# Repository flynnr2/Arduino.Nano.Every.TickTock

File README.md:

# Arduino Pendulum Timer

Capture firmware, logging and display software, and analysis tooling for high-precision pendulum timing.

## System Layout

```text
Arduino.Pendulum.Timer/
├── Nano.Every/         Precision capture firmware
├── Uno.R4.Deprecated/  Deprecated Uno receiver, retained for reference
├── Raspberry.Pi/       Pi Zero 2 W receiver, sensors, OLED and web
├── Docs/               System, protocol and component documentation
├── tests/              Capture, Pi, analysis and deprecated Uno tests
├── tools/              Minimal Nano serial capture tool
└── pendulum_analysis/  Offline clock and swing analysis
```

This is the combined repository for the complete Arduino Pendulum Timer (A.P.T)
system. The Nano Every timestamps pendulum and PPS events. A receiver handles storage,
environmental measurements, display and network access. The deprecated Uno receiver
and the Raspberry Pi replacement live here alongside the capture firmware.

- [Deprecated Uno R4 setup and validation](Uno.R4.Deprecated/README.md)
- [Raspberry Pi receiver and quickstart](Raspberry.Pi/README.md)
- [Hardware designs and prototype build files](Hardware/README.md)
- [Display repository import and provenance](Docs/Uno.R4.Deprecated/IMPORT.md)

The former `Arduino.Pendulum.Timer.Display` repository provides historical reference;
all maintained system components now belong here.

## What Is This?

The firmware captures pendulum beam-crossing edges and GPS PPS pulses on a shared ATmega4809 timer base, then emits serial timing records for host capture and offline analysis.

The repository also includes `pendulum_analysis`, a local PCPS clock and PCSW swing analysis suite.

## Why Does It Exist?

The project is intended to measure pendulum rate, stability, jitter, impulse-cycle structure, and clock/timebase health while preserving raw timing evidence for later reinterpretation.

## How Do I Build the Nano Firmware?

Open [Nano.Every/Nano.Every.ino](Nano.Every/Nano.Every.ino) in the Arduino IDE, select **Arduino Nano Every**, and build/flash.

The default build uses an external main clock on **D2/PA0**. Supply that clock
before boot at the frequency selected by the build (`F_CPU`), or build with
`USE_EXTCLK_MAIN=0` for the internal-clock path. See [wiring](Docs/Wiring.md).

The [development and validation guide](Docs/Development_and_Validation.md)
records build prerequisites, the tested board core and separate host/board checks.
With Arduino megaAVR core 1.8.8 installed, compile from the repository root:

```bash
arduino-cli compile \
  --fqbn arduino:megaavr:nona4809 \
  --build-property compiler.cpp.extra_flags="-Os -ffunction-sections -fdata-sections -flto" \
  --build-property compiler.c.extra_flags="-Os -ffunction-sections -fdata-sections -flto" \
  --build-property compiler.elf.extra_flags="-Wl,--gc-sections -flto" \
  --build-path build/nano-every \
  Nano.Every
```

## How Do I Run It?

Flash the firmware and connect the Nano to a laptop with a USB data cable.
Data and commands default to USB **`Serial` at 115200 baud**. The
[Nano capture tool](tools/README.md) writes files for later analysis:

```bash
python3 -m pip install pyserial
python3 tools/nano_capture.py --out ./my-recording
```

Use Python 3.9 or later (`python` on Windows). A single identified Nano Every
port is selected automatically; use `--list-ports` and `--port PORT` when needed.
The tool requests `emit meta` automatically, preserves received bytes in a raw
log, and writes `PCPS.CSV` and `PCSW.CSV` after validating the capture metadata.
Stop with Ctrl+C. Choose a new output directory for each recording: existing
output files are never overwritten, and storage management is yours.

The firmware emits canonical capture records for host calculation and offline
PPS calibration:

- `CFG` and `STS` metadata/status rows
- `SCH` schema declarations
- `CSW` swing rows
- `CPS` PPS rows

For continuous logging, sensor enrichment, OLED and Wi-Fi monitoring, use the
[Raspberry Pi receiver](Raspberry.Pi/README.md), with its
[OS Lite setup checklist](Raspberry.Pi/SETUP_CHECKLIST.md),
[installation guide](Raspberry.Pi/INSTALL.md), [wiring schedule](Raspberry.Pi/WIRING.md),
[GPS/chrony timekeeping plan](Raspberry.Pi/TIMEKEEPING.md) and
[recording contract](Raspberry.Pi/DATA_FORMAT.md). Its software has automated
coverage; physical Pi acceptance remains to be completed. OLED, dashboard and
ThingSpeak share a PPS-calibrated 300-swing mean. Optional
[individual-swing forecast diagnostics](Raspberry.Pi/OBSERVATORY.md#individual-swing-forecast-diagnostics)
learn a configurable repeating cycle and score predictions before learning.
They remain available through status, saved results and replay tools; the
dashboard prediction section has been removed.

Try the analysis with the checked-in synthetic recording, from the repository
root (Python 3.9 or newer):

```bash
python3 -m venv .venv
source .venv/bin/activate
python -m pip install -e .
pendulum-analyze examples/synthetic --out analysis_test/synthetic
```

Or run directly from this checkout:

```bash
python -m pendulum_analysis.suite examples/synthetic --out analysis_test/synthetic
```

Open `analysis_test/synthetic/report.html`. On Windows, activate with
`.venv\Scripts\Activate.ps1` in PowerShell. This small synthetic example checks
the workflow; it cannot demonstrate long-run stability or environmental models.
Replace `examples/synthetic` with your recording directory for real analysis;
without `--out`, output goes into its `analysis_suite` directory. Local recordings
under `Data/` are not distributed with the repository.

For multiple recording sessions, `--collection-mode combined` adds shared
statistics and gap-aware plots while retaining independently calibrated detail
reports. Add `--impulse-alignment` to compare mechanical phase across epochs;
each epoch must establish its own anchor. The default collection view remains
separate. See [combining datasets across breaks](Docs/Clock_Swing_Analysis.md#combining-valid-datasets-across-breaks).

PCPS is required; PCSW adds the swing analysis. This is the standard pendulum
analysis, available through `pendulum-analyze`. Its default report includes
PPS-calibrated periods, phase evolution, phase-15 distributions, signed phase
contributions, and rolling average/local variation with Allan/Hadamard stability.
Local variation tables include peak-to-peak range and median local standard
deviation over the same two-minute windows. Each dataset supplies its own scales
and references; interval controls do not select quiet periods automatically.
Temperature, humidity and pressure have separate matched-population fits and a
combined fit, with chronological checks and explicit coverage. The four swing
components follow the behaviour overview; environmental analysis follows them,
with capture-clock support and exposure folded away. Tables use compact display
precision and exact counts; exports retain full precision. Sections collapse
individually, with an expand/collapse-all control. Add
`--detail-start-hours 24` for a local 90-second component view,
`--autocorrelation` for persistence, `--swing-pca` or `--swing-spectra` for optional
investigations, and `--diagnostics` for extra supporting tables/charts. Raw phase
charts require `--raw-phase-charts`; polar charts require `--phase-polars`.
Neither is included by default, even with `--diagnostics`.
The fourth component adds passage speed and estimated semi-amplitude timelines,
an interactive interval explorer, complete-cycle averages, 30-half-phase profiles,
phase evolution and amplitude/period associations. Optical geometry is provisional:
`--optical-path-mm` defaults to 3.79 and `--pivot-to-beam-mm` to 1242.
Amplitude is a near-BDC harmonic estimate of centre-to-peak angle; tick/tock do
not establish physical left/right. Matched environmental comparisons test whether
mean squared amplitude improves prediction of later hours.
`--no-swing-components` omits the four components. Full CSV statistics
remain available. HTML charts and overview interactive data are embedded.
Long recordings load individual motion details in bounded chunks from the
companion `plots` folder; keep the complete report folder for detailed inspection
and downloadable CSV/JSON files.

See [Clock and swing analysis](Docs/Clock_Swing_Analysis.md) for the input contract,
bin/component mapping, settings and validation. This replaces the earlier
canonical-v2 and capture-only commands; old configuration and output schemas are
not translated. Historical analysis modules remain only for regression reference.

For tests, use the [validation guide](Docs/Development_and_Validation.md).
Whole-repository tests require Python 3.11 or newer and both packages' test
dependencies; the analysis-only installation above is not sufficient.

## Where Is Everything Else Documented?

Start with [Docs/README.md](Docs/README.md).

Primary owners:

- Wire protocol: [Docs/Protocol_Wire_Contract.md](Docs/Protocol_Wire_Contract.md)
- Data-record semantics: [Docs/Pendulum_Data_Record_Guide.md](Docs/Pendulum_Data_Record_Guide.md)
- Analysis suite: [Docs/Clock_Swing_Analysis.md](Docs/Clock_Swing_Analysis.md)
- Firmware architecture: [Docs/Implementation_Overview.md](Docs/Implementation_Overview.md)
- Hardware wiring: [Docs/Wiring.md](Docs/Wiring.md)
- Development setup and checks: [Docs/Development_and_Validation.md](Docs/Development_and_Validation.md)

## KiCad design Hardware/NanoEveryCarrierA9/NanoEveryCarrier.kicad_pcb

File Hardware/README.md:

# Hardware designs

The public hardware selection contains the current A.9 Nano Every carrier's
editable KiCad design and selected build files, plus the optical sensor mount.
These are prototypes. CAD checks and fabrication exports do not establish
electrical performance, physical fit or measured timing accuracy.

## Nano Every carrier A.9

Open [the KiCad project](NanoEveryCarrierA9/NanoEveryCarrier.kicad_pro) with
KiCad 10.0.4 or later. Native schematic sheets, PCB, local symbols, footprints
and 3D models are included. Edit these native files in KiCad; private generators
and historical bundles are not required to open them. The local library
[licence](NanoEveryCarrierA9/LICENSE-KiCad-libraries.txt) applies to included
KiCad library material.

- [Schematic PDF](NanoEveryCarrierA9/output/pdf/NanoEveryCarrier-Schematic-A9.pdf)
- [Wired schematic PDF](NanoEveryCarrierA9/output/pdf/NanoEveryCarrier-Schematic-A9-Wired.pdf)
- [Assembly and acceptance guide](NanoEveryCarrierA9/output/pdf/NanoEveryCarrier-Assembly-A9.pdf)
- [PCB-component BOM](NanoEveryCarrierA9/output/assembly/Carrier-A9-BOM.csv)
- [Accessories](NanoEveryCarrierA9/output/assembly/Carrier-A9-Accessories.csv)
- [SMD placements](NanoEveryCarrierA9/output/assembly/Carrier-A9-SMD-positions.csv)
- [Gerber/drill archive](NanoEveryCarrierA9/output/NanoEveryCarrier-A9-Gerbers.zip)

The saved PCB includes the 6 November 2026 via-clearance update. Before building,
read the assembly guide's supply-voltage, GNSS jumper, back-powering, power-path
and acceptance requirements. GNSS and TCXO regulators are separate. Remove JP2
for an independently powered GNSS receiver. Hardware files do not configure the
Nano firmware or the receiver.

Earlier A.6/A.8 wiring discussions describe their named revisions. Use the current
schematic and assembly guide for A.9 connector and power details. The
[system wiring guide](../Docs/Wiring.md) and
[Pi wiring schedule](../Raspberry.Pi/WIRING.md) describe capture connections.

## Optical sensor mount

The [mount guide](OpticalSensorMount/README.md) describes the parametric OpenSCAD
source, printable meshes and fit coupon. Confirm actual sensor dimensions and
pendulum clearances before printing a final mount.

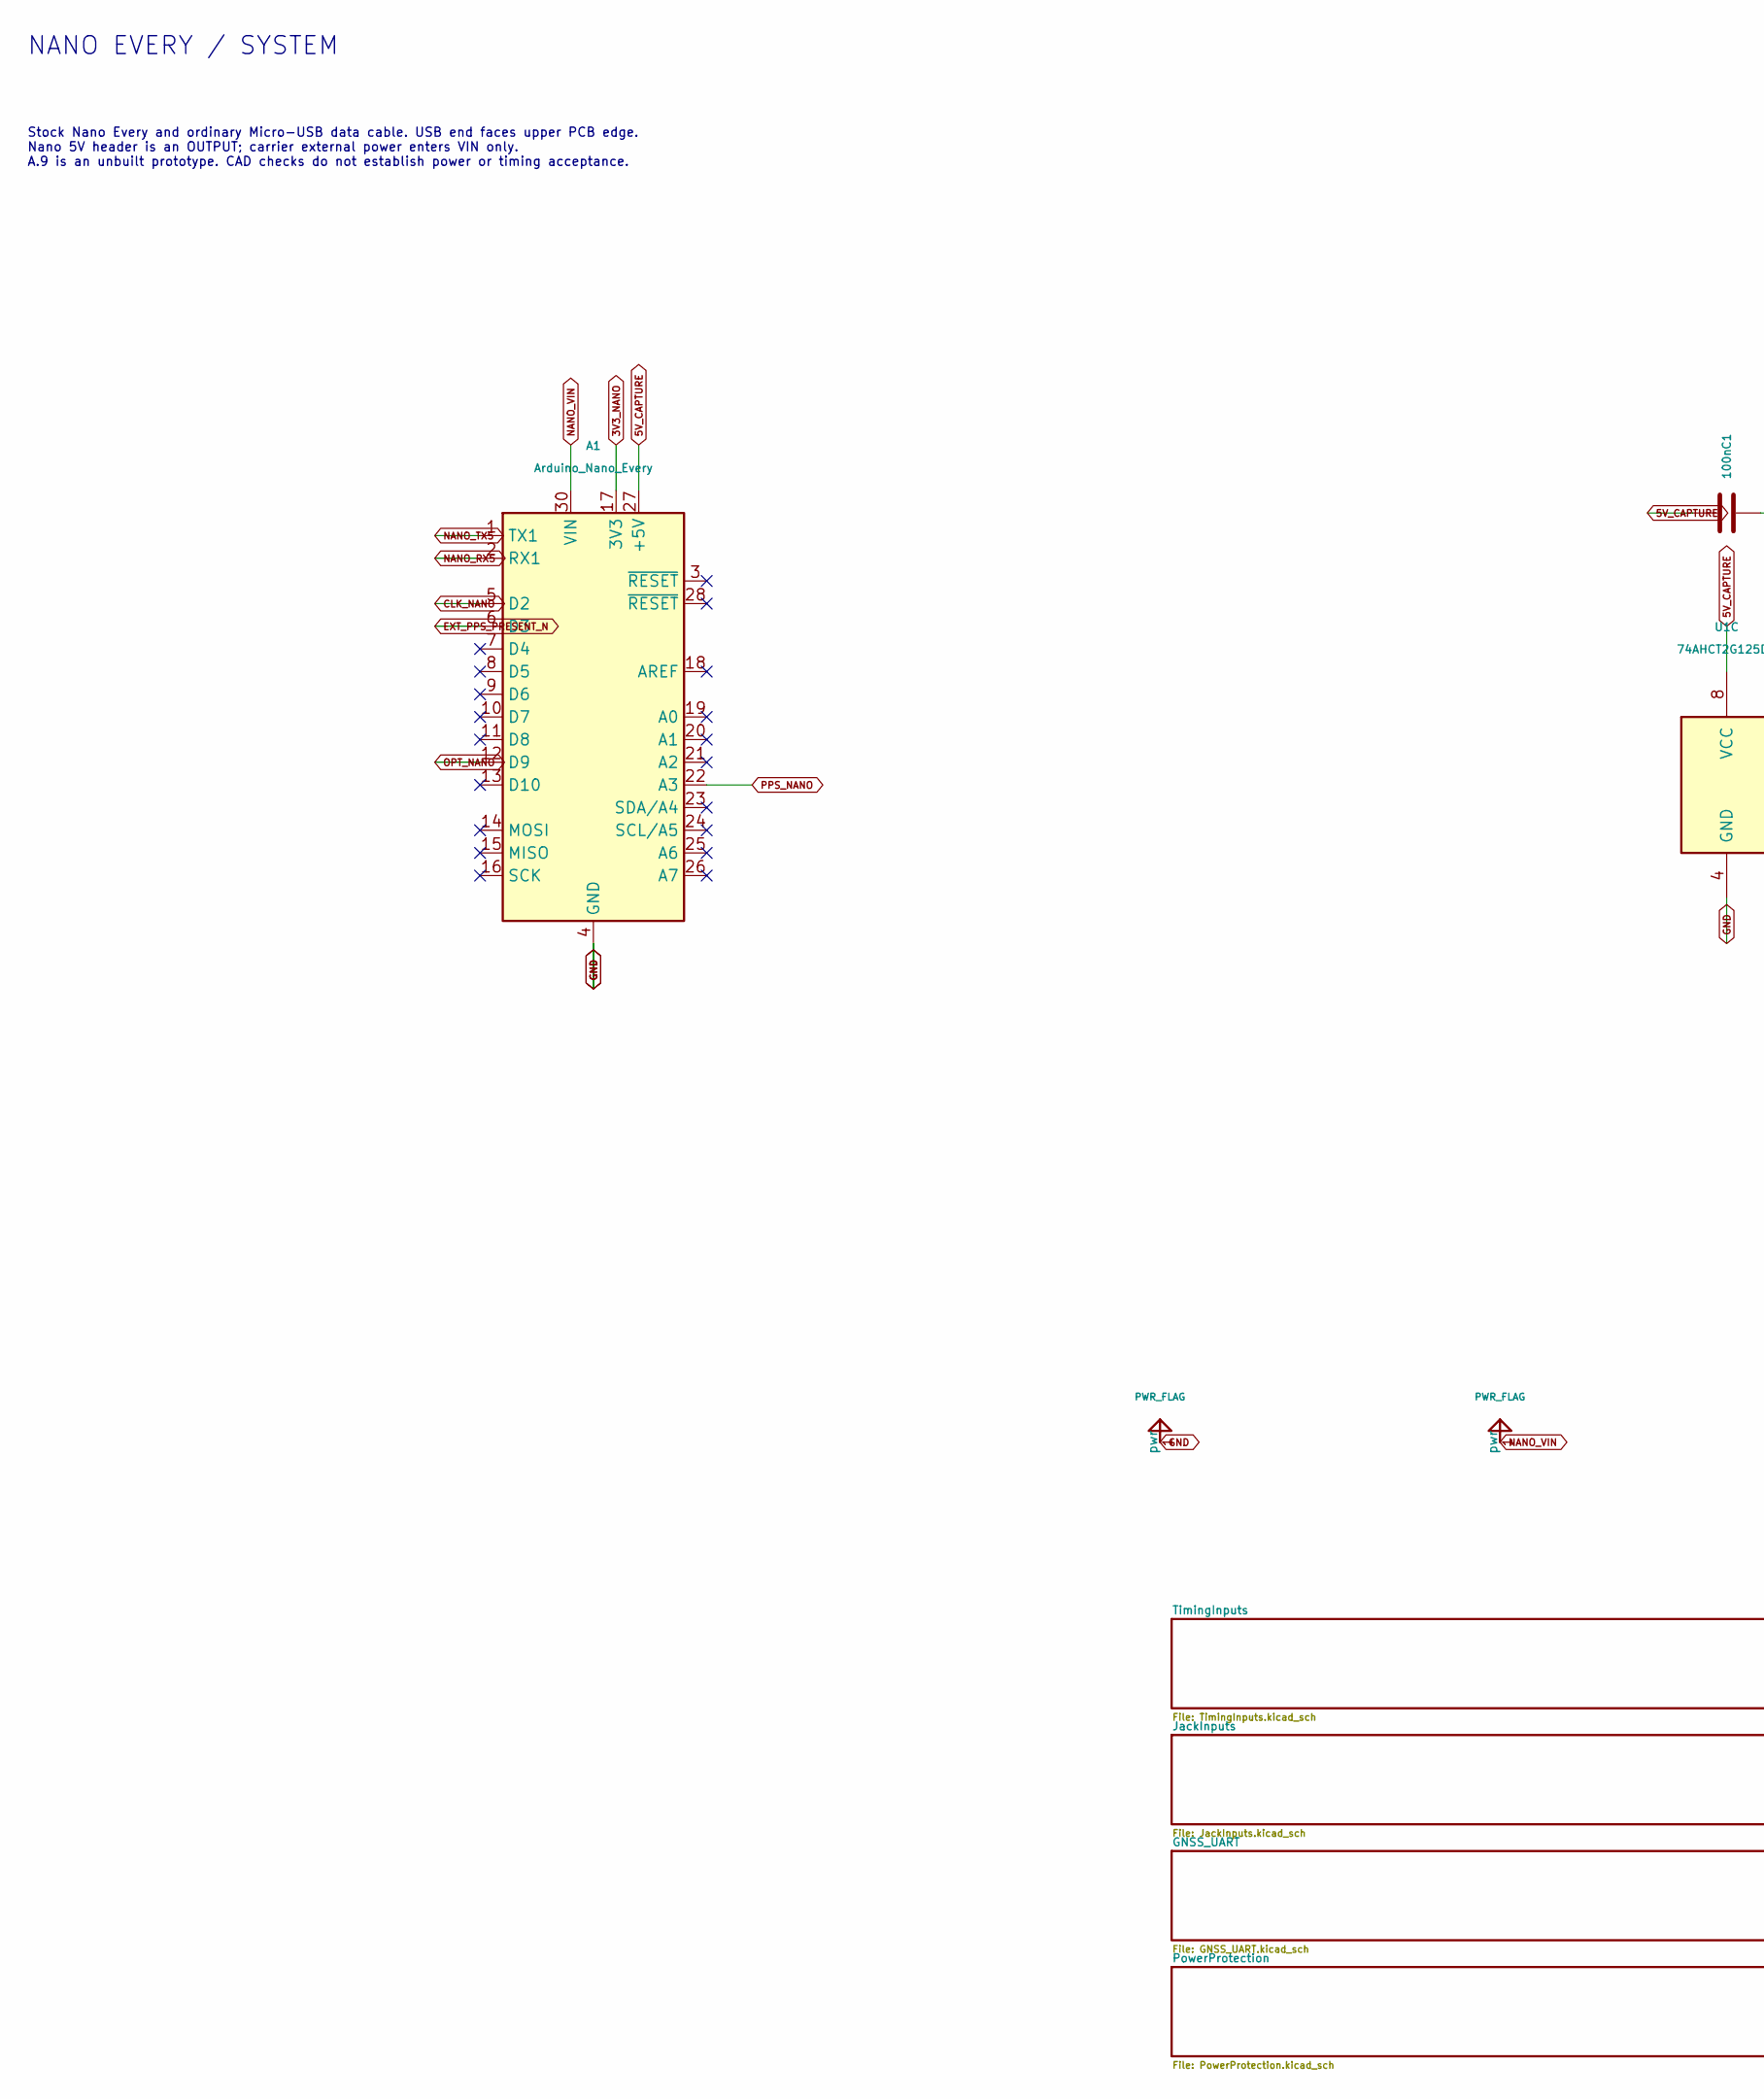
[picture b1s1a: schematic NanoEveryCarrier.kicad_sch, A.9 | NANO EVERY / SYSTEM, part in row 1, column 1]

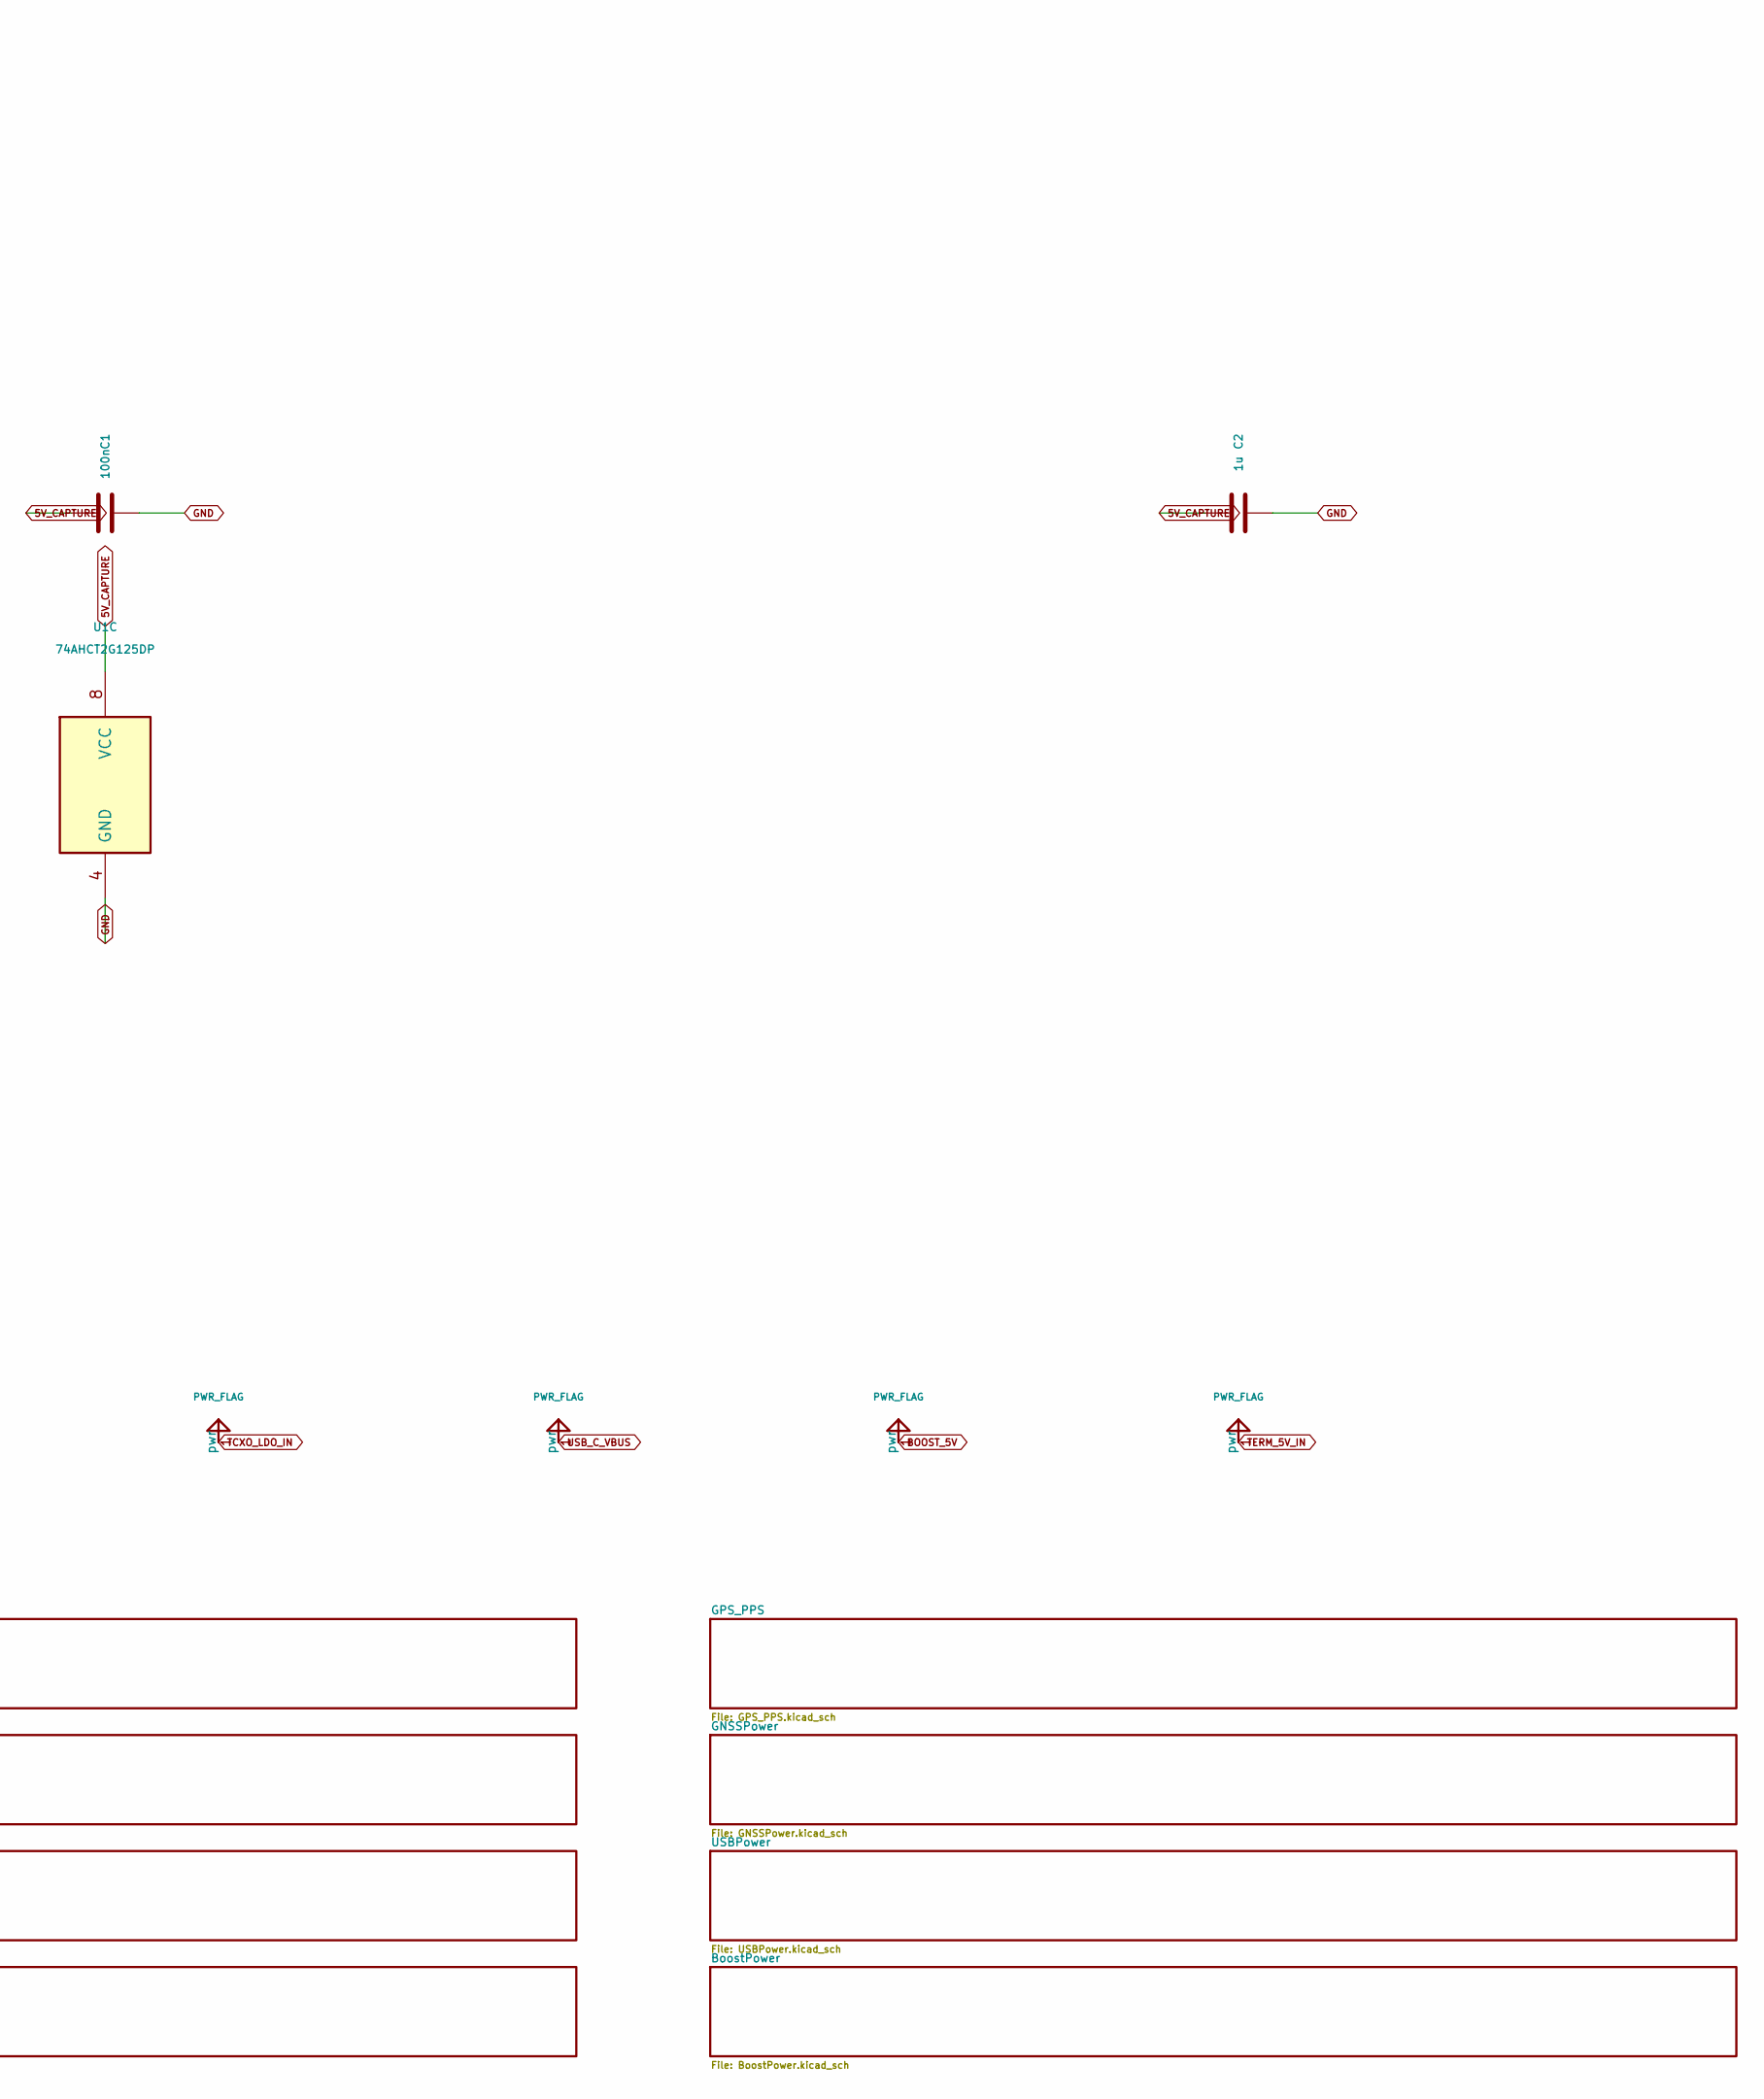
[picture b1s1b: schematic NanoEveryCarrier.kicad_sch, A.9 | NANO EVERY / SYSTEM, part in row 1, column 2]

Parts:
A1: Arduino_Nano_Every; Nano_Every_Sockets; MPN SSW-115-01-G-S
C1: 100n; C_0805_2012Metric; MPN GRM21BR71H104KA01L
C2: 1u; C_0805_2012Metric; MPN GRM21BR71C105KA01L
U1: 74AHCT2G125DP; TSSOP-8_3x3mm_P0.65mm; MPN 74AHCT2G125DP,125

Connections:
3V3_NANO: A1.17 (3V3); also elsewhere on the board
5V_CAPTURE: A1.27 (+5V), C1.1, C2.1, U1.8 (VCC); also elsewhere on the board
CLK_NANO: A1.5 (D2); also elsewhere on the board
EXT_PPS_PRESENT_N: A1.6 (D3); also elsewhere on the board
GND: A1.4 (GND), A1.29 (GND), C1.2, C2.2, U1.4 (GND); also elsewhere on the board
NANO_RX5: A1.2 (RX1); also elsewhere on the board
NANO_TX5: A1.1 (TX1); also elsewhere on the board
NANO_VIN: A1.30 (VIN); also elsewhere on the board
OPT_NANO: A1.12 (D9); also elsewhere on the board
PPS_NANO: A1.22 (A3); also elsewhere on the board

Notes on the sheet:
NANO EVERY / SYSTEM
Stock Nano Every and ordinary Micro-USB data cable. USB end faces upper PCB edge. Nano 5V header is an OUTPUT; carrier external power enters VIN only. A.9 is an unbuilt prototype. CAD checks do not establish power or timing acceptance.

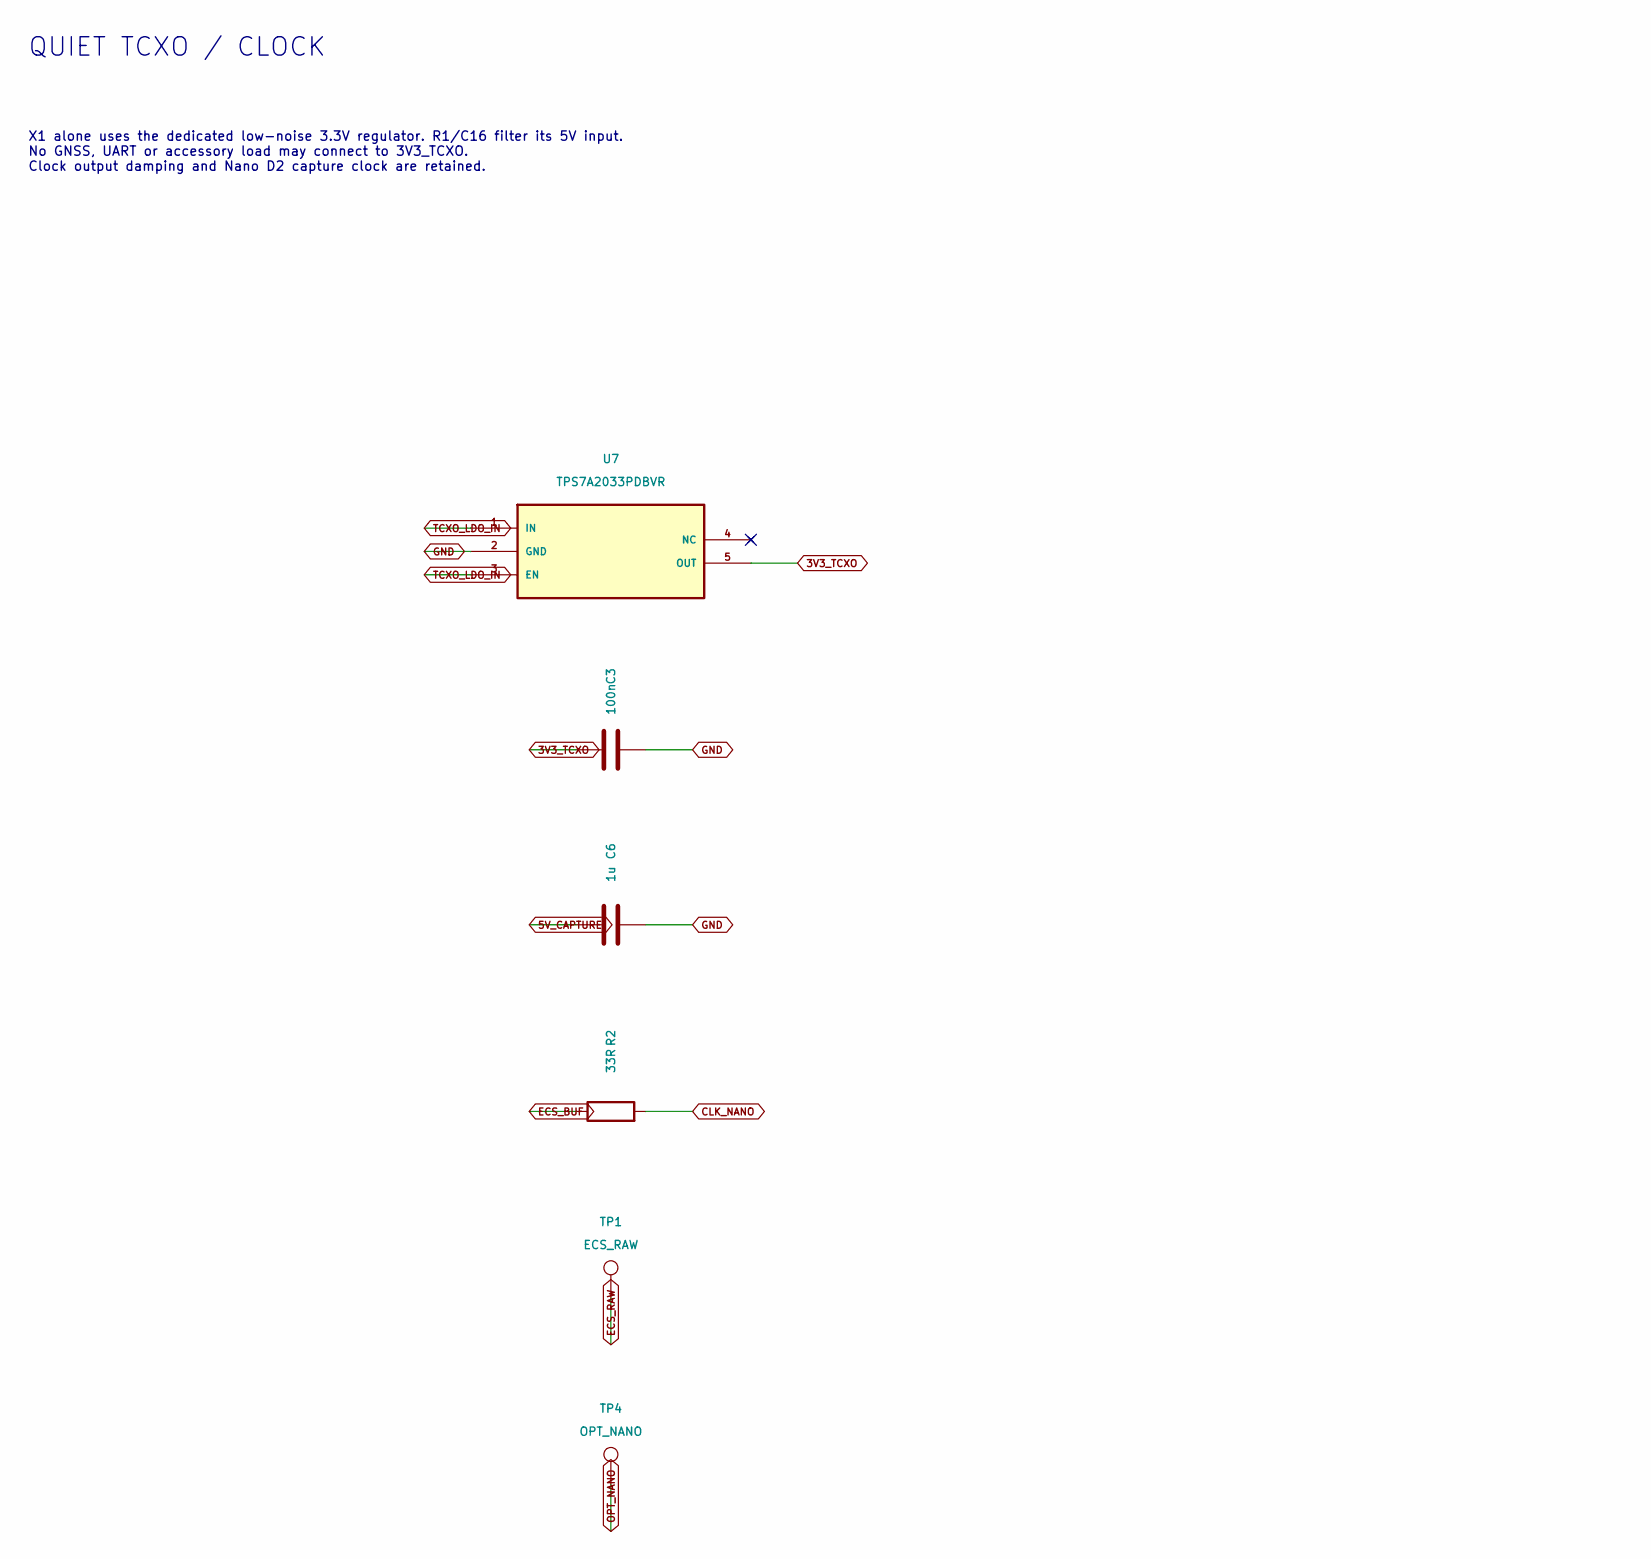
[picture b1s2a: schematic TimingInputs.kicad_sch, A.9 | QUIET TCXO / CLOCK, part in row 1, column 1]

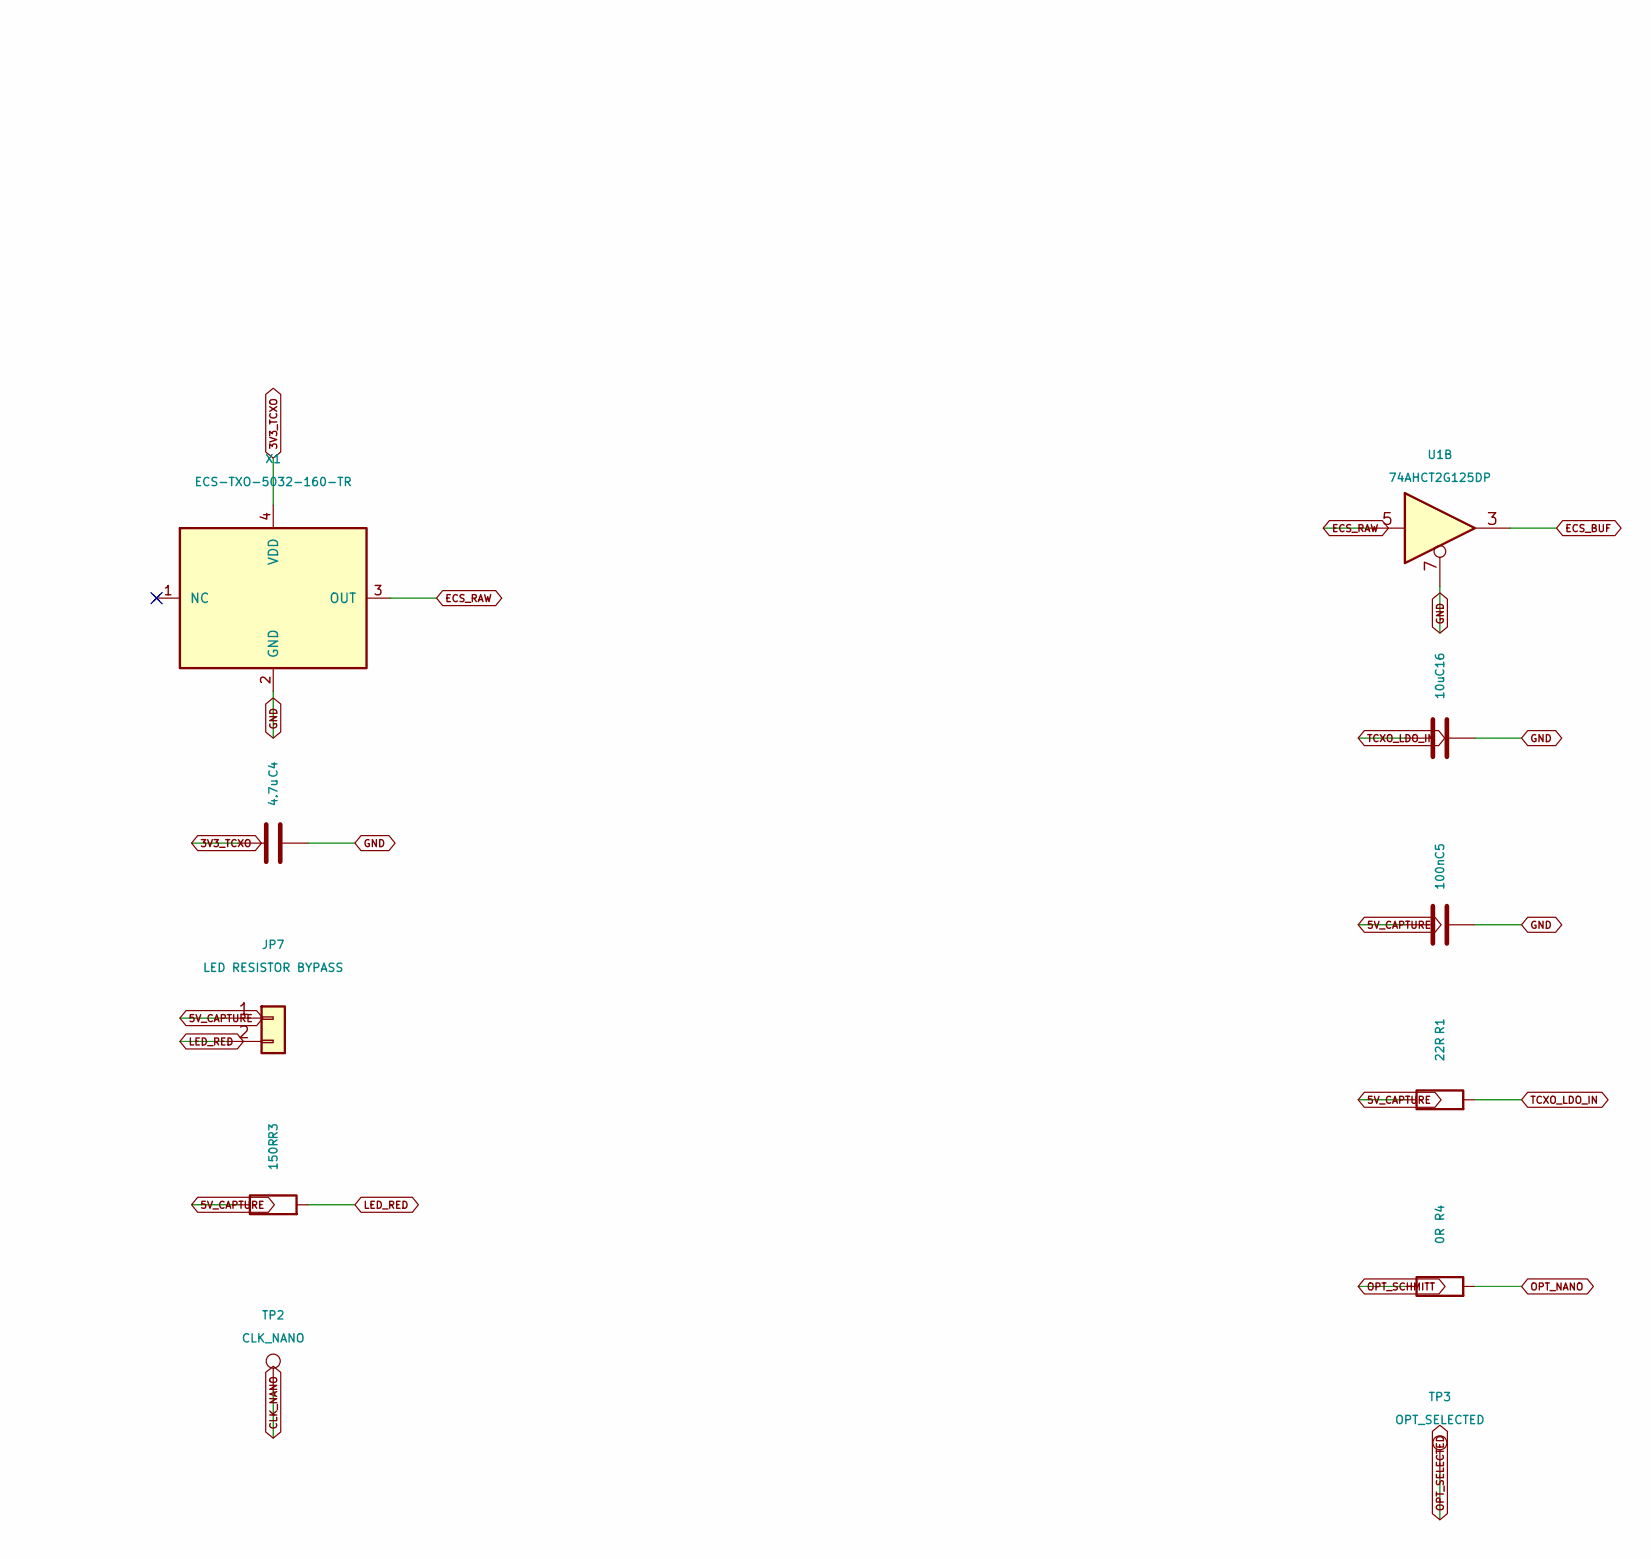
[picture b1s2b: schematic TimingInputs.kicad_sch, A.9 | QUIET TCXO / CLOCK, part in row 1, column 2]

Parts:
C3, C5: 100n; C_0805_2012Metric; MPN GRM21BR71H104KA01L
C4: 4.7u; C_0805_2012Metric; MPN GRM21BR71C475KA73L
C6: 1u; C_0805_2012Metric; MPN GRM21BR71C105KA01L
C16: 10u; C_0805_2012Metric; MPN GRM21BR61C106KE15L
JP7: LED RESISTOR BYPASS; PinHeader_1x02_P2.54mm_Vertical; MPN TSW-102-07-G-S
R1: 22R; R_0805_2012Metric; MPN RC0805FR-0722RL
R2: 33R; R_1206_3216Metric_Pad1.30x1.75mm_HandSolder; MPN RC1206FR-0733RL
R3: 150R; R_1206_3216Metric; MPN RC1206FR-07150RL
R4: 0R; R_1206_3216Metric_Pad1.30x1.75mm_HandSolder; MPN RC1206JR-070RL
TP1: ECS_RAW; TestPoint_Pad_D1.0mm
TP2: CLK_NANO; TestPoint_Pad_D1.0mm
TP3: OPT_SELECTED; TestPoint_Pad_D1.0mm
TP4: OPT_NANO; TestPoint_Pad_D1.0mm
U1: 74AHCT2G125DP; TSSOP-8_3x3mm_P0.65mm; MPN 74AHCT2G125DP,125
U7: TPS7A2033PDBVR; SOT-23-5; MPN TPS7A2033PDBVR
X1: ECS-TXO-5032-160-TR; ECS_TXO_5032; MPN ECS-TXO-5032-160-TR

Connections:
3V3_TCXO: C3.1, C4.1, U7.5 (OUT), X1.4 (VDD); also elsewhere on the board
5V_CAPTURE: C5.1, C6.1, JP7.1, R1.1, R3.1; also elsewhere on the board
CLK_NANO: R2.2, TP2.1; also elsewhere on the board
ECS_BUF: R2.1, U1.3
ECS_RAW: TP1.1, U1.5, X1.3 (OUT)
GND: C3.2, C4.2, C5.2, C6.2, C16.2, U1.7, U7.2 (GND), X1.2 (GND); also elsewhere on the board
LED_RED: JP7.2, R3.2; also elsewhere on the board
OPT_NANO: R4.2, TP4.1; also elsewhere on the board
OPT_SCHMITT: R4.1; also elsewhere on the board
OPT_SELECTED: TP3.1; also elsewhere on the board
TCXO_LDO_IN: C16.1, R1.2, U7.1 (IN), U7.3 (EN)

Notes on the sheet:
QUIET TCXO / CLOCK
X1 alone uses the dedicated low-noise 3.3V regulator. R1/C16 filter its 5V input. No GNSS, UART or accessory load may connect to 3V3_TCXO. Clock output damping and Nano D2 capture clock are retained.
